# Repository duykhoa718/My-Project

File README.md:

This is the workplace for designing a buck converter with 6.8V and 30A current max.
This circuit is used for serving the 12 servo Miuzel 20kg torque with a current load from 2-3A 
The purpose of using 12 servos is to design a 12 servo with enough power supply and connect it to the Jetson Orin Nano to control the movement
The input power source is only designed for a 3s LiPo battery so far. We can test it with a 4s Lipo, but the main point is with a 3s Lipo right now.

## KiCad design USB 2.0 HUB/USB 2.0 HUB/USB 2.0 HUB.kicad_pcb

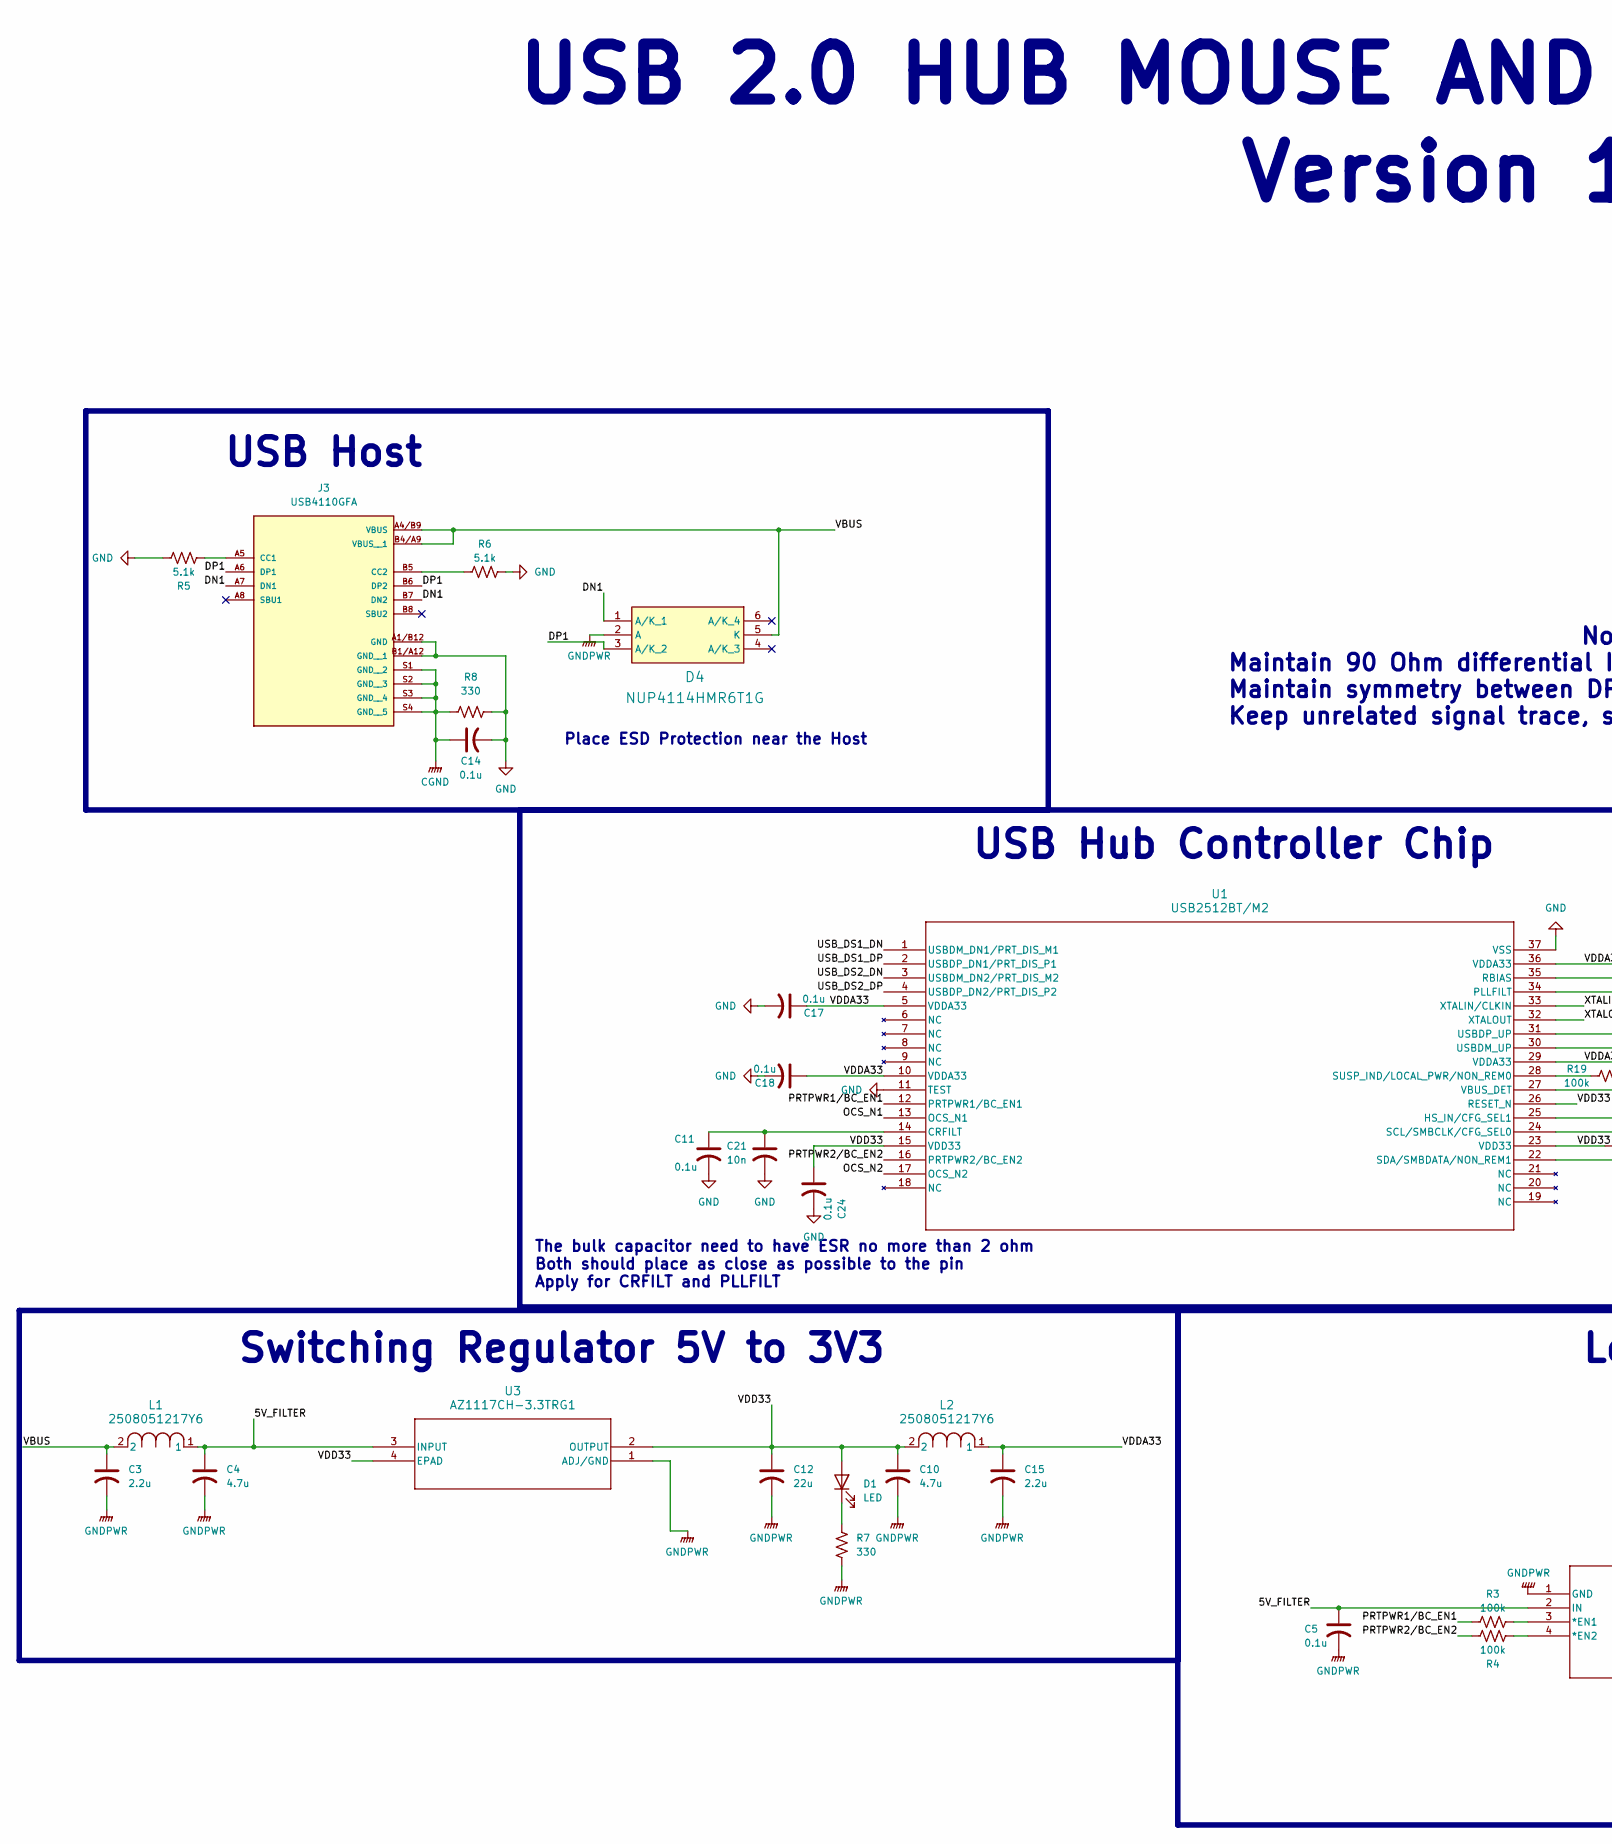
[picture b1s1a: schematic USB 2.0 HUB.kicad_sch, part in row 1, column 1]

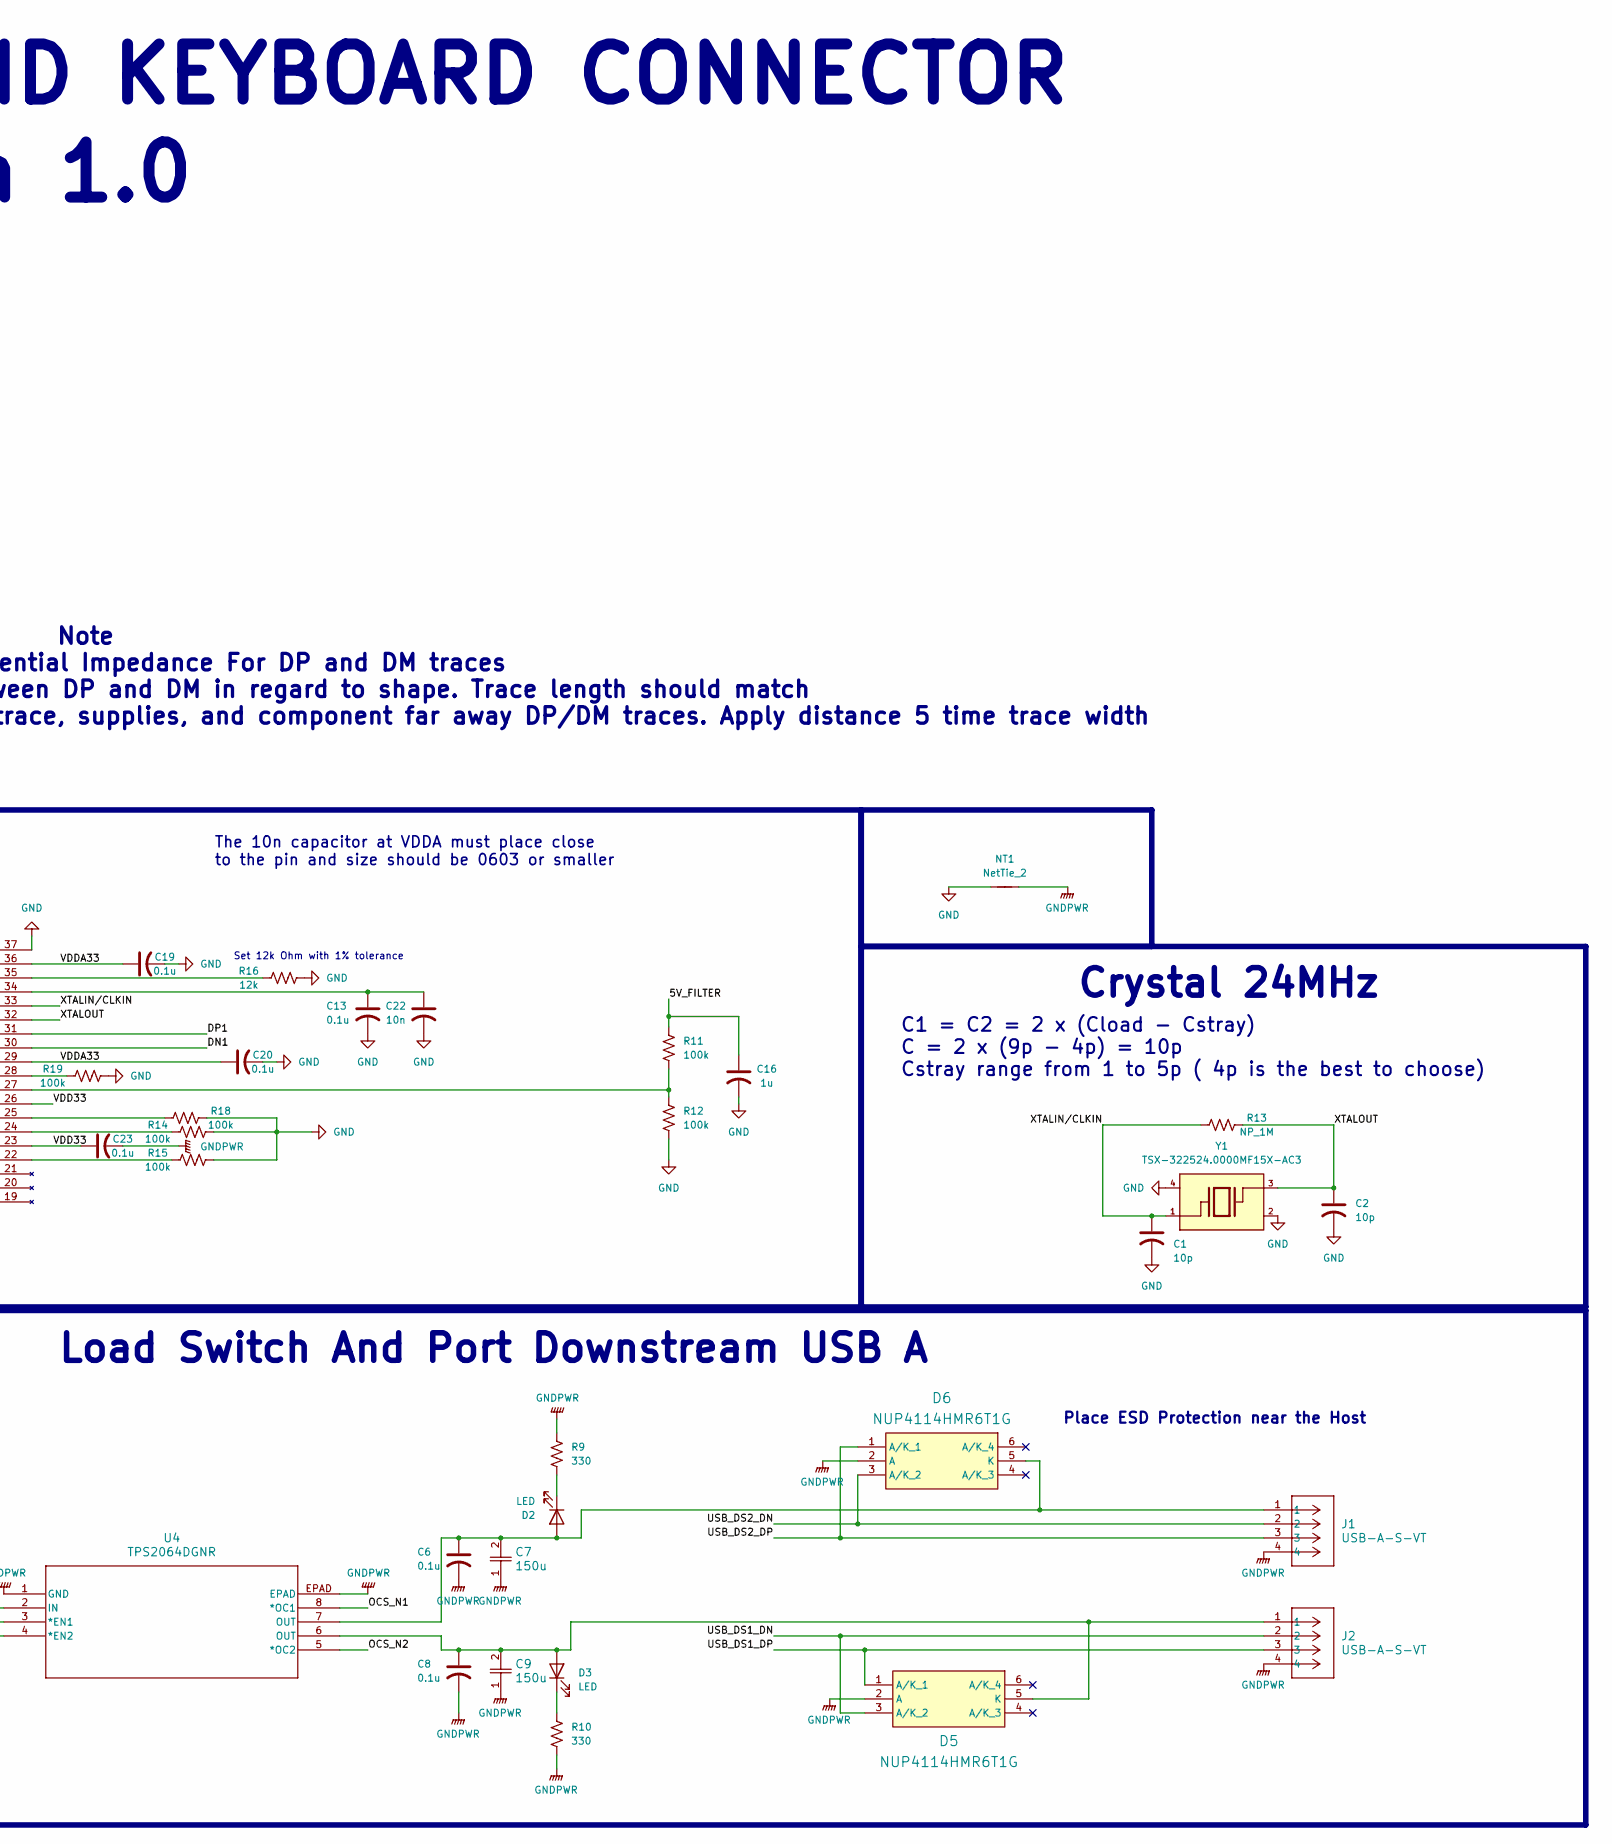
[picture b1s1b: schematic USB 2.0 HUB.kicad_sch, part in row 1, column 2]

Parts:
C1, C2: 10p; C_0402_1005Metric_Pad0.74x0.62mm_HandSolder
C3, C15: 2.2u; C_0603_1608Metric_Pad1.08x0.95mm_HandSolder
C4, C10: 4.7u; C_0805_2012Metric_Pad1.18x1.45mm_HandSolder
C5, C6, C8, C11, C13, C14: 0.1u; C_0805_2012Metric_Pad1.18x1.45mm_HandSolder
C7, C9: 150u; CAP_A768MS_KEM
C12: 22u; C_1206_3216Metric_Pad1.33x1.80mm_HandSolder
C16: 1u; C_0603_1608Metric_Pad1.08x0.95mm_HandSolder
C17, C18, C19, C20, C23, C24: 0.1u; C_0603_1608Metric_Pad1.08x0.95mm_HandSolder
C21, C22: 10n; C_0402_1005Metric_Pad0.74x0.62mm_HandSolder
D1, D2, D3: LED; LED_0805_2012Metric_Pad1.15x1.40mm_HandSolder
D4, D5, D6: NUP4114HMR6T1G; SOT95P275X110-6N; Manufacturer_Part_Number NUP4114HMR6T1G; Mouser Part Number 863-NUP4114HMR6T1G
J1, J2: USB-A-S-VT; CONN_USB-A-S-VT_ADM
J3: USB4110GFA; GCT_USB4110GFA
L1, L2: 2508051217Y6; IND_25_0805_FRT
NT1: NetTie_2; NetTie-2_SMD_Pad0.5mm
R3, R4, R11, R12, R14, R15, R18, R19: 100k; R_0603_1608Metric_Pad0.98x0.95mm_HandSolder
R5, R6: 5.1k; R_0603_1608Metric_Pad0.98x0.95mm_HandSolder
R7, R8, R9, R10: 330; R_0603_1608Metric_Pad0.98x0.95mm_HandSolder
R13: NP_1M; R_0402_1005Metric_Pad0.72x0.64mm_HandSolder
R16: 12k; R_0603_1608Metric_Pad0.98x0.95mm_HandSolder
U1: USB2512BT/M2; 36SQFN-3706-6X6B_MCH
U3: AZ1117CH-3.3TRG1; SOT-223_DIO
U4: TPS2064DGNR; DGN8_1P89X1P57
Y1: TSX-322524.0000MF15X-AC3; OSCCC320X250X60; PARTREV N/A

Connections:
/5V_FILTER: C4.1, C5.1, C16.1, L1.1, R11.2, U3.3 (INPUT), U4.2 (IN)
/DN1: D4.1 (A/K_1), J3.A7 (DN1), J3.B7 (DN2), U1.30 (USBDM_UP)
/DP1: D4.3 (A/K_2), J3.A6 (DP1), J3.B6 (DP2), U1.31 (USBDP_UP)
/OCS_N1: U1.13 (OCS_N1), U4.8 (*OC1)
/OCS_N2: U1.17 (OCS_N2), U4.5 (*OC2)
/PRTPWR1/BC_EN1: R3.1, U1.12 (PRTPWR1/BC_EN1)
/PRTPWR2/BC_EN2: R4.1, U1.16 (PRTPWR2/BC_EN2)
/USB_DS1_DN: D5.3 (A/K_2), J2.2, U1.1 (USBDM_DN1/PRT_DIS_M1)
/USB_DS1_DP: D5.1 (A/K_1), J2.3, U1.2 (USBDP_DN1/PRT_DIS_P1)
/USB_DS2_DN: D6.3 (A/K_2), J1.2, U1.3 (USBDM_DN2/PRT_DIS_M2)
/USB_DS2_DP: D6.1 (A/K_1), J1.3, U1.4 (USBDP_DN2/PRT_DIS_P2)
/VBUS: C3.1, D4.5 (K), J3.A4/B9 (VBUS), J3.B4/A9 (VBUS__1), L1.2
/VDD33: C10.1, C12.1, C23.1, C24.1, D1.2 (A), L2.2, U1.15 (VDD33), U1.23 (VDD33), U1.26 (RESET_N), U3.2 (OUTPUT), U3.4 (EPAD)
/VDDA33: C15.1, C17.1, C18.1, C19.1, C20.1, L2.1, U1.5 (VDDA33), U1.10 (VDDA33), U1.29 (VDDA33), U1.36 (VDDA33)
/XTALIN/CLKIN: C1.1, R13.1, U1.33 (XTALIN/CLKIN), Y1.1
/XTALOUT: C2.1, R13.2, U1.32 (XTALOUT), Y1.3
CGND: C14.1, J3.S1 (GND__2), J3.S2 (GND__3), J3.S3 (GND__4), J3.S4 (GND__5), R8.1
GND: C1.2, C2.2, C11.2, C13.2, C14.2, C16.2, C17.2, C18.2, C19.2, C20.2, C21.2, C22.2, C24.2, J3.A1/B12 (GND), J3.B1/A12 (GND__1), NT1.1, R5.1, R6.1, R8.2, R12.1, R14.1, R15.1, R16.1, R18.1, R19.1, U1.11 (TEST), U1.37 (VSS), Y1.2, Y1.4
GNDPWR: C3.2, C4.2, C5.2, C6.2, C7.1, C8.2, C9.1, C10.2, C12.2, C15.2, C23.2, D4.2 (A), D5.2 (A), D6.2 (A), J1.4, J2.4, NT1.2, R7.2, R9.2, R10.2, U3.1 (ADJ/GND), U4.1 (GND), U4.EPAD
unnamed: D1.1 (K), R7.1
unnamed: C6.1, C7.2, D2.2 (A), D6.5 (K), J1.1, U4.7 (OUT)
unnamed: D2.1 (K), R9.1
unnamed: C8.1, C9.2, D3.2 (A), D5.5 (K), J2.1, U4.6 (OUT)
unnamed: D3.1 (K), R10.1
unnamed: J3.A5 (CC1), R5.2
unnamed: J3.B5 (CC2), R6.2
unnamed: C11.1, C21.1, U1.14 (CRFILT)
unnamed: R18.2, U1.25 (HS_IN/CFG_SEL1)
unnamed: C13.1, C22.1, U1.34 (PLLFILT)
unnamed: R16.2, U1.35 (RBIAS)
unnamed: R14.2, U1.24 (SCL/SMBCLK/CFG_SEL0)
unnamed: R15.2, U1.22 (SDA/SMBDATA/NON_REM1)
unnamed: R19.2, U1.28 (SUSP_IND/LOCAL_PWR/NON_REM0)
unnamed: R11.1, R12.2, U1.27 (VBUS_DET)
unnamed: R3.2, U4.3 (*EN1)
unnamed: R4.2, U4.4 (*EN2)

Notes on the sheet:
Crystal 24MHz
The 10n capacitor at VDDA must place close to the pin and size should be 0603 or smaller
Load Switch And Port Downstream USB A
Version 1.0
Place ESD Protection near the Host
Note Maintain 90 Ohm differential Impedance For DP and DM traces Maintain symmetry between DP and DM in regard to shape. Trace length should match Keep unrelated signal trace, supplies, and component far away DP/DM traces. Apply distance 5 time trace width
USB Host
The bulk capacitor need to have ESR no more than 2 ohm Both should place as close as possible to the pin Apply for CRFILT and PLLFILT
Set 12k Ohm with 1% tolerance
USB 2.0 HUB MOUSE AND KEYBOARD CONNECTOR
C1 = C2 = 2 x (Cload - Cstray) C = 2 x (9p - 4p) = 10p Cstray range from 1 to 5p ( 4p is the best to choose)
Switching Regulator 5V to 3V3
USB Hub Controller Chip

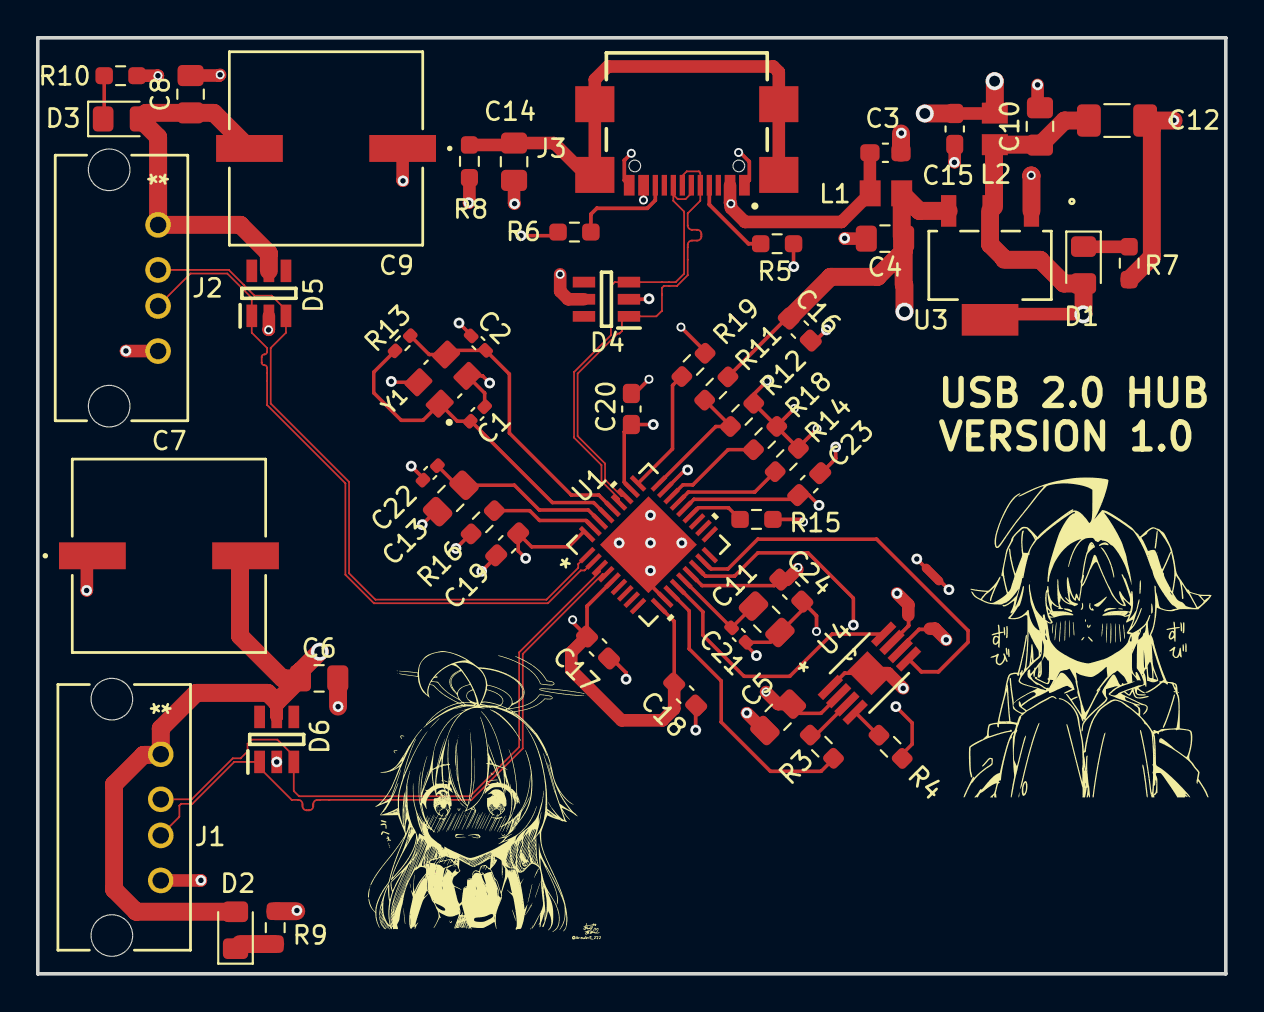
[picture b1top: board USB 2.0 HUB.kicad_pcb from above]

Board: 4 copper layers, 66.0 x 52.0 mm, 56 parts (0 on the bottom side), 36 nets.

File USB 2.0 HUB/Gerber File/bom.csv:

Designator,Footprint,Quantity,Value,LCSC Part #
"C1, C2",0402,2,10p,
"C10, C4",0805,2,4.7u,
"C11, C13, C14, C5, C6, C8",0805,6,0.1u,
C12,1206,1,22u,
"C15, C3",0603,2,2.2u,
C16,0603,1,1u,
"C17, C18, C19, C20, C23, C24",0603,6,0.1u,
"C21, C22",0402,2,10n,
"C7, C9",CAP_A768MS_KEM,2,150u,
"D1, D2, D3",0805,3,LED,
"D4, D5, D6",SOT95P275X110-6N,3,NUP4114HMR6T1G,
"J1, J2",CONN_USB-A-S-VT_ADM,2,USB-A-S-VT,
J3,GCT_USB4110GFA,1,USB4110GFA,
"L1, L2",IND_25_0805_FRT,2,2508051217Y6,
R1,0603,1,634,
"R10, R7, R8, R9",0603,4,330,
"R11, R12, R14, R15, R18, R19, R3, R4",0603,8,100k,
R13,0402,1,NP_1M,
R16,0603,1,12k,
R2,0603,1,1k,
"R5, R6",0603,2,5.1k,
U1,36SQFN-3706-6X6B_MCH,1,USB2512BT/M2,
U3,SOT-223_DIO,1,AZ1117CH-3.3TRG1,
U4,DGN8_1P89X1P57,1,TPS2064DGNR,
Y1,OSCCC320X250X60,1,TSX-322524.0000MF15X-AC3,

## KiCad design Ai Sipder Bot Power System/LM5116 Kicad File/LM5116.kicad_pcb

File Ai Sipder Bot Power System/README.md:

This is the workplace for designing a buck converter with 6.8V and 20A current max.
This circuit is used for serving the 12 servo Miuzel 20kg torque with a current load from 1-2A 
The purpose of using 12 servos is to design a 12 servo with enough power supply and connect it to the Jetson Orin Nano to control the movement
The input power source is only designed for a 5s LiPo battery.

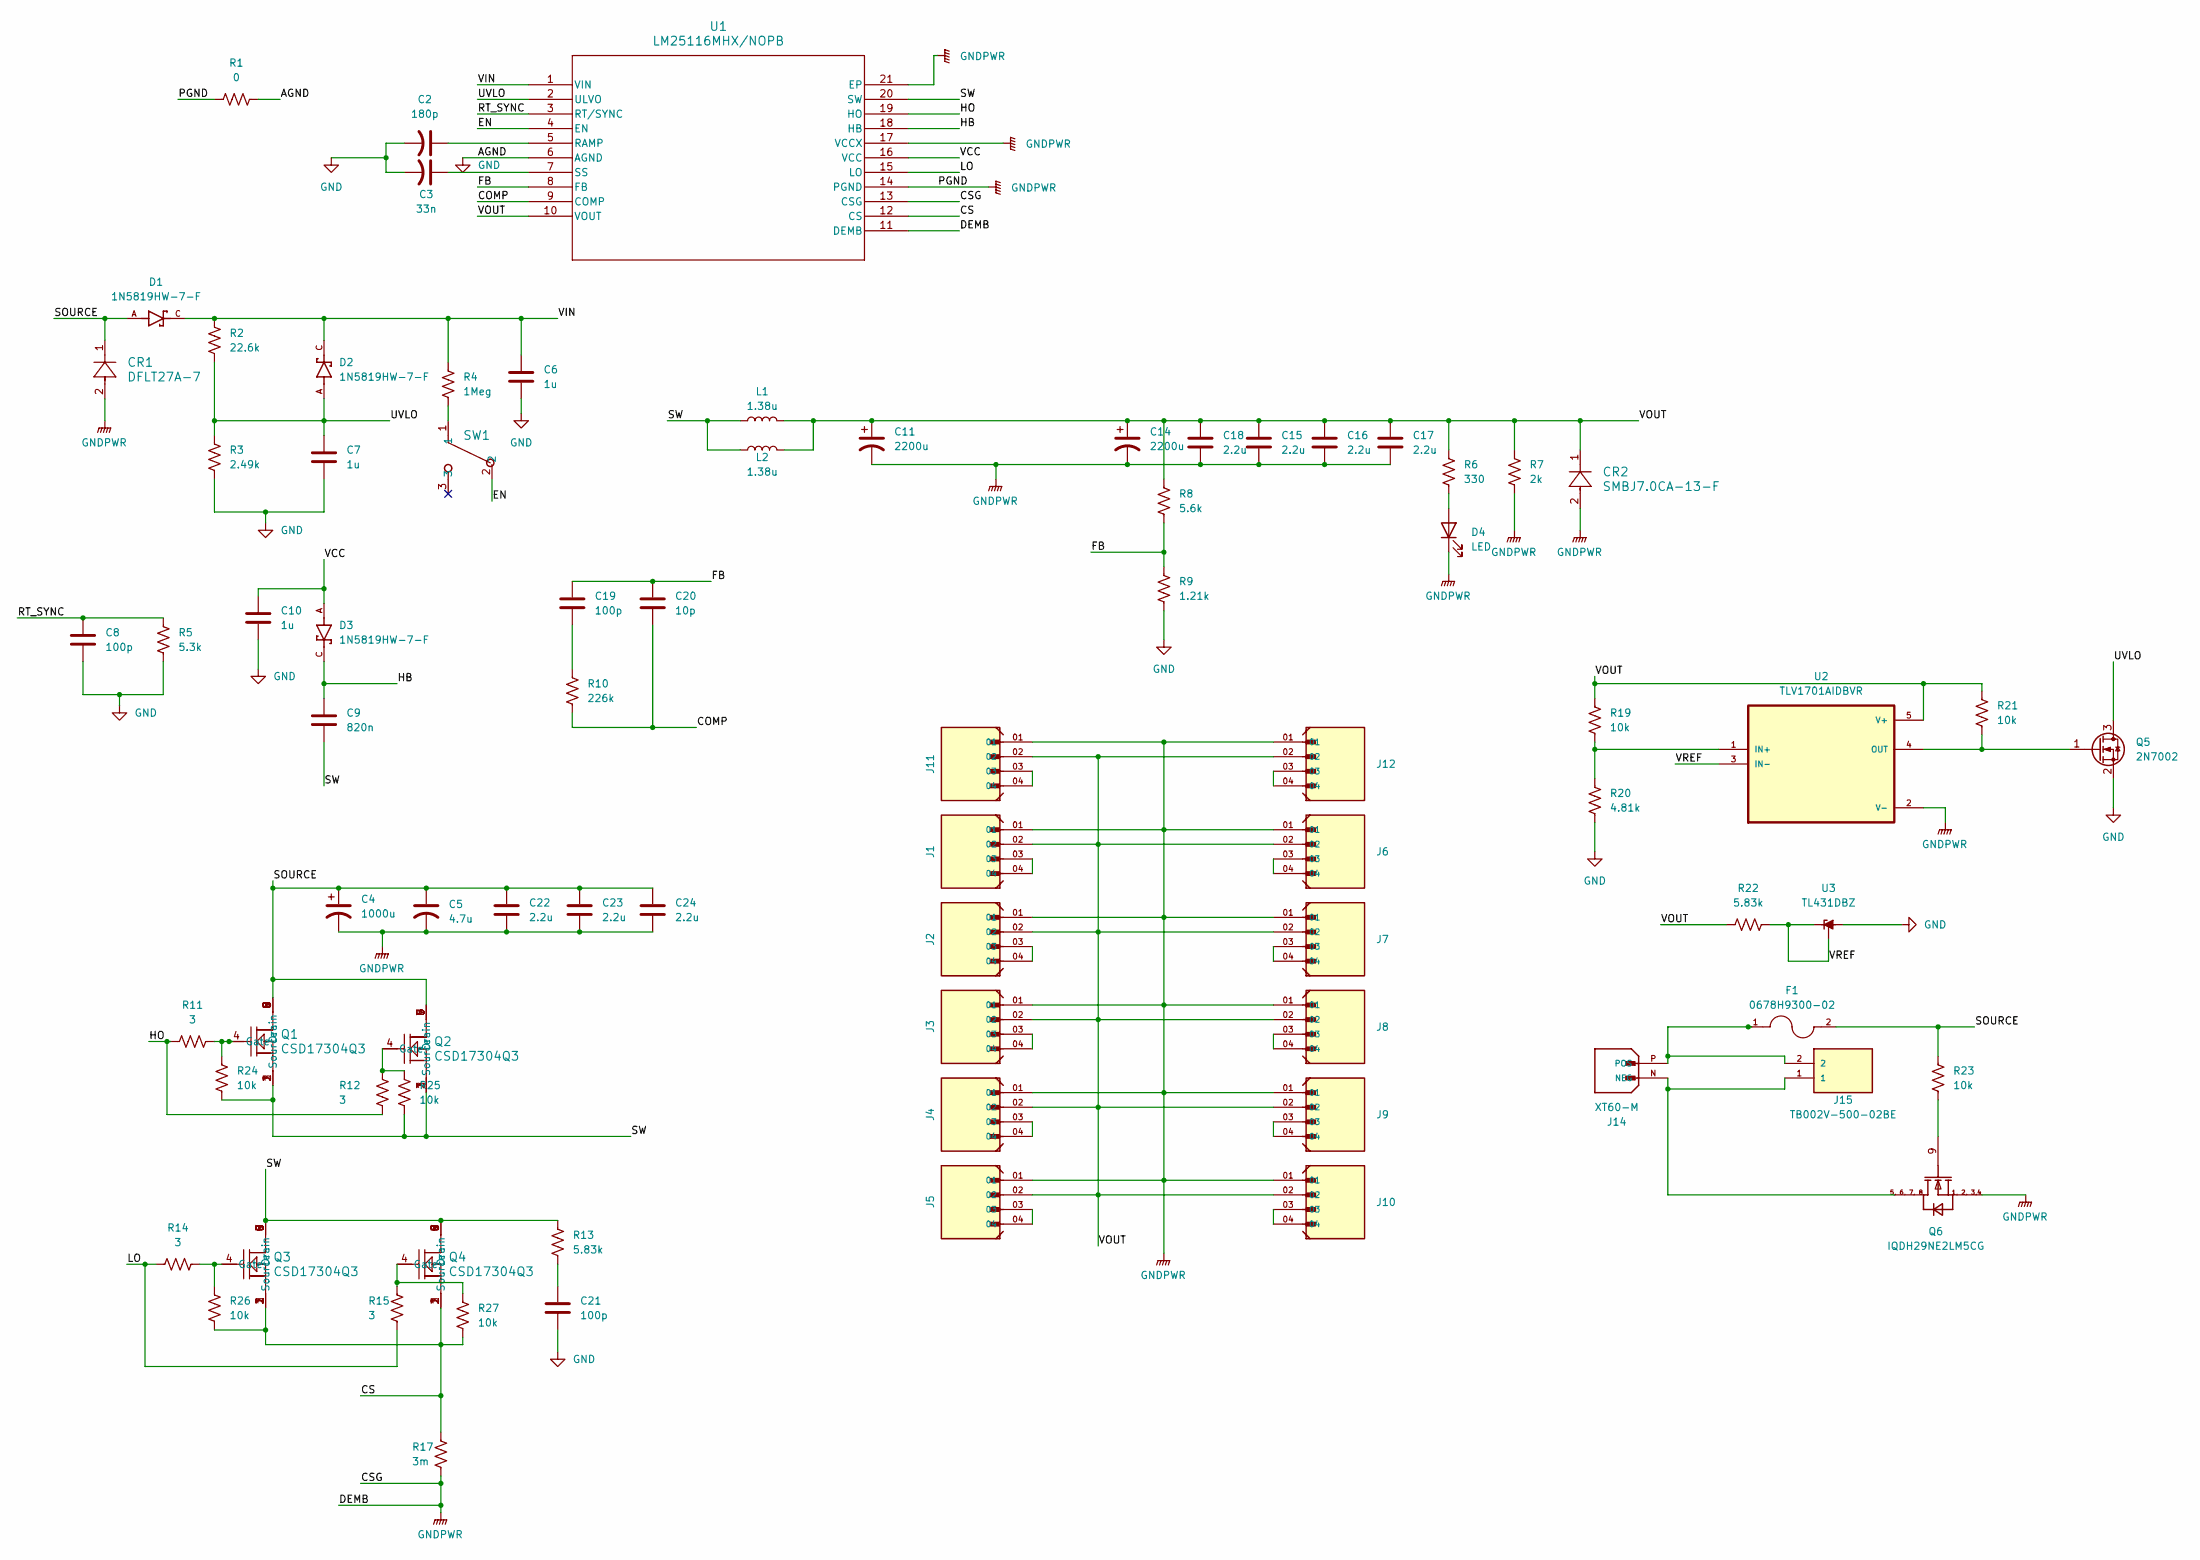
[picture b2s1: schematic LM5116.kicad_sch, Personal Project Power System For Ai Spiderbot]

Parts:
C2: 180p; C_0603_1608Metric_Pad1.08x0.95mm_HandSolder
C3: 33n; C_1206_3216Metric_Pad1.33x1.80mm_HandSolder
C4: 1000u; CP_Radial_D10.0mm_P5.00mm
C5: 4.7u; C_0805_2012Metric_Pad1.18x1.45mm_HandSolder
C6, C7, C10: 1u; C_0603_1608Metric_Pad1.08x0.95mm_HandSolder
C8, C19, C21: 100p; C_0603_1608Metric_Pad1.08x0.95mm_HandSolder
C9: 820n; C_0603_1608Metric_Pad1.08x0.95mm_HandSolder
C11, C14: 2200u; CP_Radial_D10.0mm_P5.00mm
C15, C16, C17, C18, C22, C23, C24: 2.2u; C_0603_1608Metric_Pad1.08x0.95mm_HandSolder
C20: 10p; C_0603_1608Metric_Pad1.08x0.95mm_HandSolder
CR1: DFLT27A-7; CR_LT27A-7_DIO
CR2: SMBJ7.0CA-13-F; SMB_DIO
D1, D2, D3: 1N5819HW-7-F; SOD3715X145N; PARTREV 18-2
D4: LED; LED_0603_1608Metric_Pad1.05x0.95mm_HandSolder
F1: 0678H9300-02; FUSC9830X318N; PARTREV Dec2019
J1, J2, J3, J4, J5, J6, J7, J8, J9, J10, J11, J12: 61300411121; WURTH_61300411121
J14: XT60-M; AMASS_XT60-M; PARTREV V1.2
J15: TB002V-500-02BE; CUI_TB002V-500-02BE
L1, L2: 1.38u; L_Pulse_PA4341
Q1, Q2, Q3, Q4: CSD17304Q3; DQG0008A
Q5: 2N7002; SOT-23_Handsoldering
Q6: IQDH29NE2LM5CG; IFX-PG-TTFN-9-2-V
R1: 0; R_0402_1005Metric_Pad0.72x0.64mm_HandSolder
R2: 22.6k; R_0805_2012Metric_Pad1.20x1.40mm_HandSolder
R3: 2.49k; R_0805_2012Metric_Pad1.20x1.40mm_HandSolder
R4: 1Meg; R_0402_1005Metric_Pad0.72x0.64mm_HandSolder
R5: 5.3k; R_0603_1608Metric_Pad0.98x0.95mm_HandSolder
R6: 330; R_0603_1608Metric_Pad0.98x0.95mm_HandSolder
R7: 2k; R_0603_1608Metric_Pad0.98x0.95mm_HandSolder
R8: 5.6k; R_0603_1608Metric_Pad0.98x0.95mm_HandSolder
R9: 1.21k; R_0603_1608Metric_Pad0.98x0.95mm_HandSolder
R10: 226k; R_0603_1608Metric_Pad0.98x0.95mm_HandSolder
R11, R12, R14, R15: 3; R_0603_1608Metric_Pad0.98x0.95mm_HandSolder
R13, R22: 5.83k; R_0603_1608Metric_Pad0.98x0.95mm_HandSolder
R17: 3m; R_2512_6332Metric_Pad1.40x3.35mm_HandSolder
R19, R21, R23, R24, R25, R26, R27: 10k; R_0603_1608Metric_Pad0.98x0.95mm_HandSolder
R20: 4.81k; R_0805_2012Metric_Pad1.20x1.40mm_HandSolder
SW1: EG1218; SW_1218_EWI
U1: LM25116MHX/NOPB; MXA20A_TEX-M
U2: TLV1701AIDBVR; SOT95P280X145-5N
U3: TL431DBZ; SOT-23_Handsoldering

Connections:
/COMP: C20.2, R10.2, U1.9 (COMP)
/CS: Q3.1 (Source), Q3.2, Q3.3, Q4.1 (Source), Q4.2, Q4.3, R17.2, R26.1, R27.1, U1.12 (CS)
/FB: C19.1, C20.1, R8.2, R9.1, U1.8 (FB)
/HB: C9.1, D3.C, U1.18 (HB)
/HO: R11.1, R12.2, U1.19 (HO)
/LO: R14.1, R15.1, U1.15 (LO)
/RT_SYNC: C8.1, R5.1, U1.3 (RT/SYNC)
/SOURCE: C4.1, C5.1, C22.1, C23.1, C24.1, CR1.1, D1.A, F1.2, Q1.5 (Drain), Q1.6, Q1.7, Q1.8, Q1.9, Q2.5 (Drain), Q2.6, Q2.7, Q2.8, Q2.9, R23.2
/SW: C9.2, L1.1, L2.1, Q1.1 (Source), Q1.2, Q1.3, Q2.1 (Source), Q2.2, Q2.3, Q3.5 (Drain), Q3.6, Q3.7, Q3.8, Q3.9, Q4.5 (Drain), Q4.6, Q4.7, Q4.8, Q4.9, R13.1, R24.1, R25.1, U1.20 (SW)
/UVLO: C7.1, D2.A, Q5.3 (D), R2.2, R3.1, U1.2 (ULVO)
/VCC: C10.1, D3.A, U1.16 (VCC)
/VIN: C6.1, D1.C, D2.C, R2.1, R4.1, U1.1 (VIN)
/VOUT: C11.1, C14.1, C15.1, C16.1, C17.1, C18.1, CR2.1, J1.02, J2.02, J3.02, J4.02, J5.02, J6.02, J7.02, J8.02, J9.02, J10.02, J11.02, J12.02, L1.2, L2.2, R6.1, R7.1, R8.1, R19.1, R21.1, R22.1, U1.10 (VOUT), U2.5 (V+)
/VREF: R22.2, U2.3 (IN-), U3.1 (K), U3.2 (REF)
GND: C2.2, C3.2, C6.2, C7.2, C8.2, C10.2, C21.2, Q5.2 (S), R1.2, R3.2, R5.2, R9.2, R20.2, SW1.3, U1.6 (AGND), U3.3 (A)
GNDPWR: C4.2, C5.2, C11.2, C14.2, C15.2, C16.2, C17.2, C18.2, C22.2, C23.2, C24.2, CR1.2, CR2.2, D4.1 (K), J1.01, J2.01, J3.01, J4.01, J5.01, J6.01, J7.01, J8.01, J9.01, J10.01, J11.01, J12.01, Q6.1 (SOURCE1), Q6.2 (SOURCE2), Q6.3 (SOURCE3), Q6.4 (SOURCE4), R1.1, R7.2, R17.1, U1.11 (DEMB), U1.13 (CSG), U1.14 (PGND), U1.17 (VCCX), U1.21 (EP), U2.2 (V-)
unnamed: C19.2, R10.1
unnamed: C21.1, R13.2
unnamed: D4.2 (A), R6.2
unnamed: J1.03, J1.04
unnamed: J2.03, J2.04
unnamed: J3.03, J3.04
unnamed: J4.03, J4.04
unnamed: J5.03, J5.04
unnamed: J6.03, J6.04
unnamed: J7.03, J7.04
unnamed: J8.03, J8.04
unnamed: J9.03, J9.04
unnamed: J10.03, J10.04
unnamed: J11.03, J11.04
unnamed: J12.03, J12.04
unnamed: J14.N (NEG), J15.1, Q6.5 (DRAIN1), Q6.6 (DRAIN2), Q6.7 (DRAIN3), Q6.8 (DRAIN4)
unnamed: F1.1, J14.P (POS), J15.2
unnamed: Q1.4 (Gate), R11.2, R24.2
unnamed: Q2.4 (Gate), R12.1, R25.2
unnamed: Q3.4 (Gate), R14.2, R26.2
unnamed: Q4.4 (Gate), R15.2, R27.2
unnamed: Q5.1 (G), R21.2, U2.4 (OUT)
unnamed: Q6.9 (GATE), R23.1
unnamed: C2.1, U1.5 (RAMP)
unnamed: C3.1, U1.7 (SS)
unnamed: R19.2, R20.1, U2.1 (IN+)

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
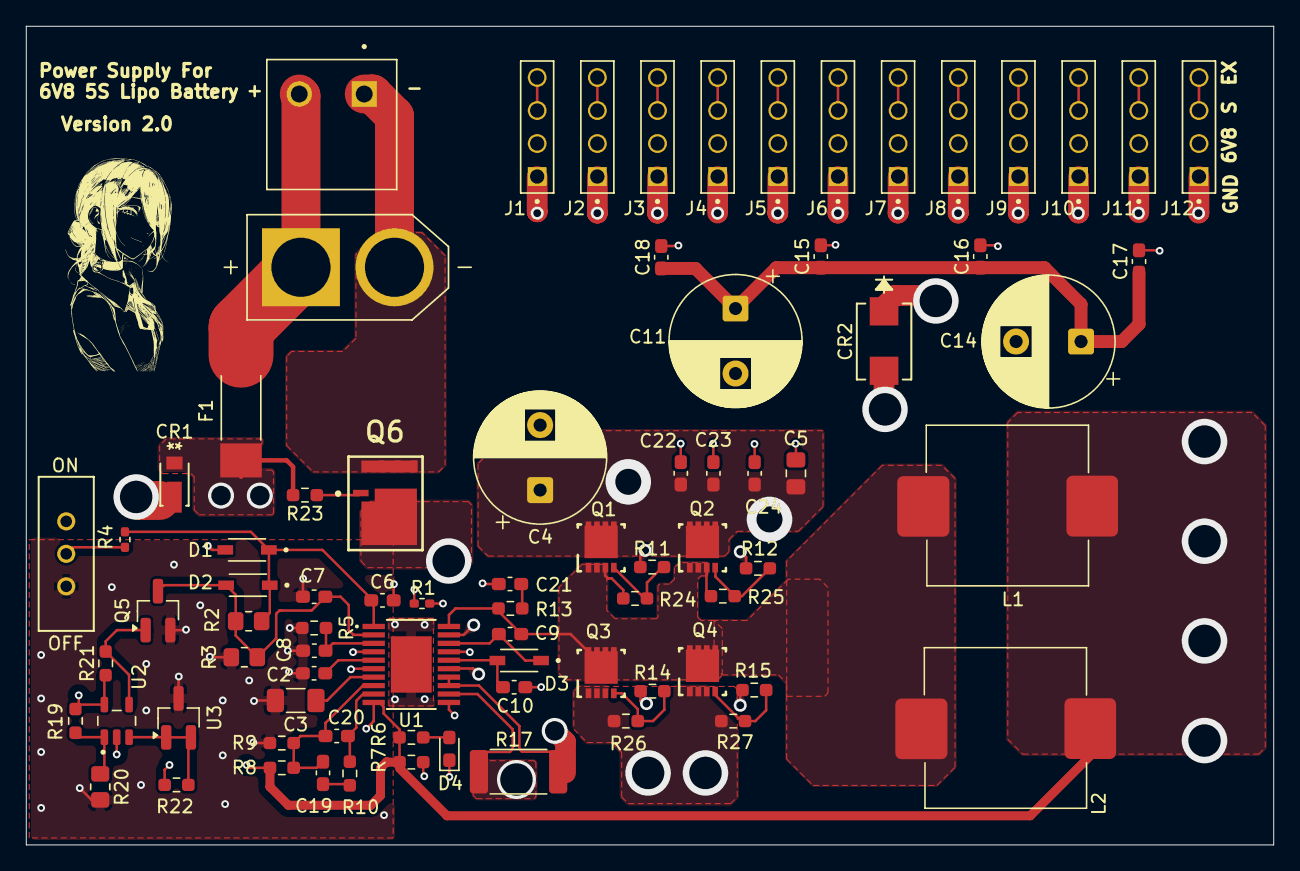
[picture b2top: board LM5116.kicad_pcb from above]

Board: 4 copper layers, 96.0 x 63.0 mm, 79 parts (0 on the bottom side), 44 nets.

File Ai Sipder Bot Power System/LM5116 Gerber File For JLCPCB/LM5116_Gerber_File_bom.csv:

Designator,Footprint,Quantity,Value,LCSC Part #
"C10, C6, C7",0603,3,1u,
"C11, C14",CP_Radial_D10.0mm_P5.00mm,2,2200u,
"C15, C16, C17, C18, C22, C23, C24",0603,7,2.2u,
"C19, C21, C8",0603,3,100p,
C2,0603,1,180p,
C20,0603,1,10p,
C3,1206,1,33n,
C4,CP_Radial_D10.0mm_P5.00mm,1,1000u,
C5,0805,1,4.7u,
C9,0603,1,820n,
CR1,CR_LT27A-7_DIO,1,DFLT27A-7,
CR2,SMB_DIO,1,SMBJ7.0CA-13-F,
"D1, D2, D3",SOD3715X145N,3,1N5819HW-7-F,
D4,0603,1,LED,
F1,FUSC9830X318N,1,0678H9300-02,
"J1, J10, J11, J12, J2, J3, J4, J5, J6, J7, J8, J9",WURTH_61300411121,12,61300411121,
J14,AMASS_XT60-M,1,XT60-M,
J15,CUI_TB002V-500-02BE,1,TB002V-500-02BE,
"L1, L2",L_Pulse_PA4341,2,1.38u,
"Q1, Q2, Q3, Q4",DQG0008A,4,CSD17304Q3,
Q5,SOT-23_Handsoldering,1,2N7002,
Q6,IFX-PG-TTFN-9-2-V,1,IQDH29NE2LM5CG,
R1,0402,1,0,
R10,0603,1,226k,
"R11, R12, R14, R15",0603,4,3,
"R13, R22",0603,2,5.83k,
R17,2512,1,3m,
"R19, R21, R23, R24, R25, R26, R27",0603,7,10k,
R2,0805,1,22.6k,
R20,0805,1,4.81k,
R3,0805,1,2.49k,
R4,0402,1,1Meg,
R5,0603,1,5.3k,
R6,0603,1,330,
R7,0603,1,2k,
R8,0603,1,5.6k,
R9,0603,1,1.21k,
SW1,SW_1218_EWI,1,EG1218,
U1,MXA20A_TEX-M,1,LM25116MHX/NOPB,
U2,SOT95P280X145-5N,1,TLV1701AIDBVR,
U3,SOT-23_Handsoldering,1,TL431DBZ,

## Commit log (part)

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2026-06-18 Change Name
2026-06-19 Add Component List
2026-06-19 Add List Component
2026-06-22 Add Component File
2026-06-24 Add Switch
2026-06-26 Add dot for LED
2026-06-26 Initialize README with project details
    Added project description for buck converter design.
2026-06-27 New Kicad File Final
2026-06-27 Add Kicad File
2026-06-29 Update Footprint
2026-06-30 Update Kicad File
2026-06-30 Update Component List
2026-06-30 Update buck converter specifications in README
2026-06-30 Update Adding pulldown resistor
